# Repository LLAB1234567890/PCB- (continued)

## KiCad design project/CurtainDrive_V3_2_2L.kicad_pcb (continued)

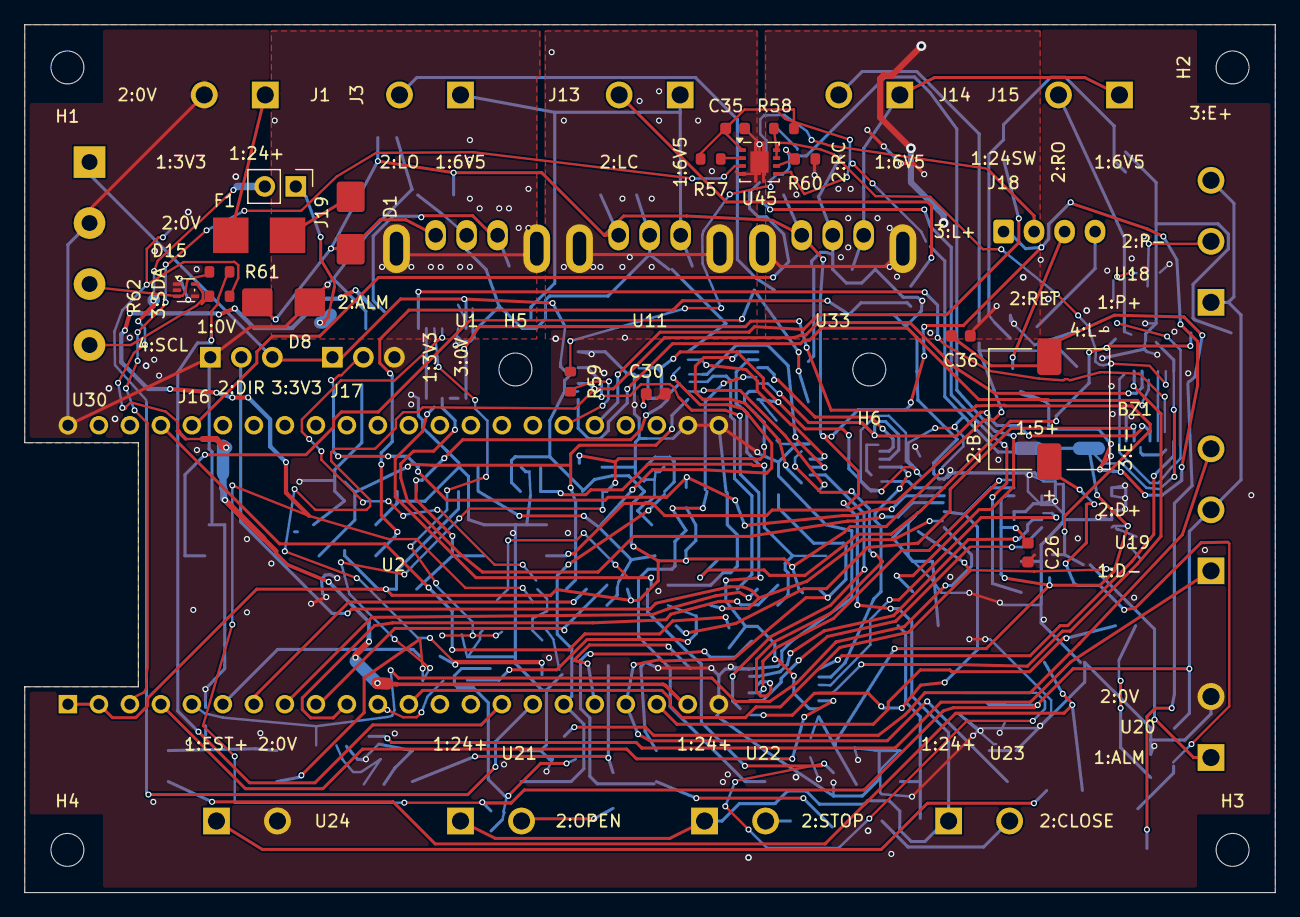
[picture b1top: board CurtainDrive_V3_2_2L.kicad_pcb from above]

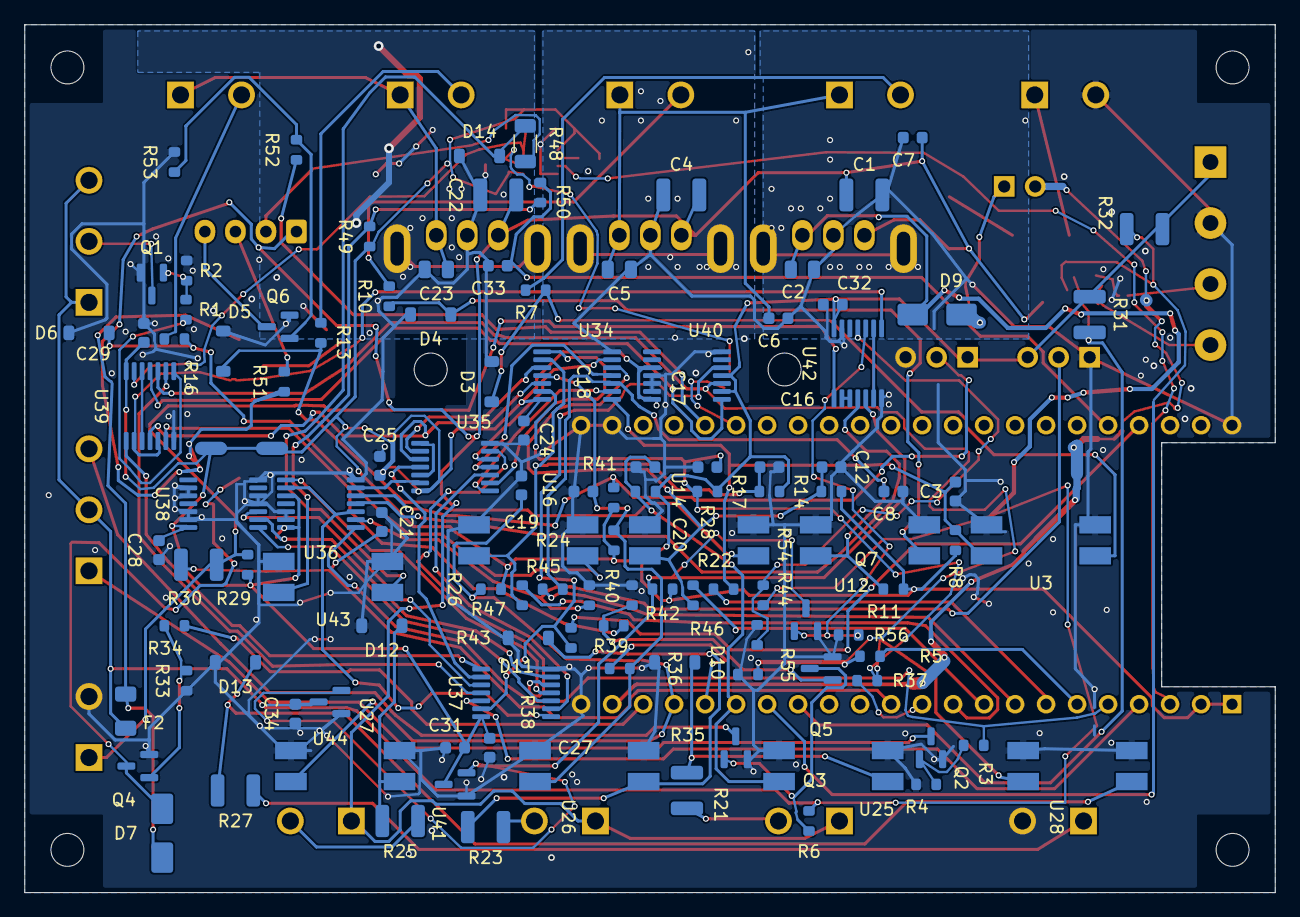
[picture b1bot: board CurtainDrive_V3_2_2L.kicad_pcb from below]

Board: 2 copper layers, 102.5 x 71.1 mm, 157 parts (114 on the bottom side), 110 nets.

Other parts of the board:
H1, H2, H3, H4, H5, H6: M2.5 NPTH; MountingHole_2.7mm_M2.5

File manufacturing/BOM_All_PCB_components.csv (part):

Designator,Value,Footprint,MPN,Manufacturer,LCSC,Assembly,Note
U2,ESP32-S3-DEVKITC-1-N8R8,ESP32_S3_DevKitC_1_N8R8,ESP32-S3-DEVKITC-1-N8R8,ESPRESSIF,C20541519,Manual,"ESP32-S3 DevKitC-1 v1.1 N8R8. GPIO4 STEP, GPIO5 DIR, GPIO6 ARM, GPIO1 RUN feedback, GPIO2 SET, GPIO21 lamp, GPIO47 watchdog. Pads32-34 GPIO35-37 unavailable with PSRAM. J19 power link must be removed for ordinary USB powering."
C1,10uF 100V,C_1210_3225Metric,C3225X7R2A106K250AC,TDK,C3883958,SMT,厂家特性表已核对；10uF标称，需按24V直流偏压复核实际电容
C2,22uF 10V,C_0805_2012Metric,CL21A226MPQNNNE,SAMSUNG(三星),C29277,SMT,
C4,10uF 100V,C_1210_3225Metric,C3225X7R2A106K250AC,TDK,C3883958,SMT,厂家特性表已核对；10uF标称，需按24V直流偏压复核实际电容
C5,22uF 10V,C_0805_2012Metric,CL21A226MPQNNNE,SAMSUNG(三星),C29277,SMT,
C6,100nF 50V,C_0603_1608Metric,CC0603KRX7R9BB104,YAGEO,C14663,SMT,
C7,100nF 50V,C_0603_1608Metric,CC0603KRX7R9BB104,YAGEO,C14663,SMT,
C22,10uF 100V,C_1210_3225Metric,C3225X7R2A106K250AC,TDK,C3883958,SMT,厂家特性表已核对；10uF标称，需按24V直流偏压复核实际电容
C23,22uF 10V,C_0805_2012Metric,CL21A226MPQNNNE,SAMSUNG,C29277,SMT,
D1,SS36-E3/57T,D_SMB,SS36-E3/57T,VISHAY(威世),C35722,SMT,反接保护，阳极2接保险丝，阴极1接板内24V
D8,SMBJ26A,D_SMB,SMBJ26A-13-F,DIODES,C135062,SMT,
D9,SS14,D_SMA,SS14,MDD,C2480,SMT,
F1,1A fast,Source_F1,0451001.MRL,Littelfuse(美国力特),C3099,SMT,
J1,KF301-5.0-2P,Source_J1,KF301-5.0-2P,KEFA(科发),C474881,Manual,
U1,K78U05-1000R3,K78U05_1000R3,K78U05-1000R3,MORNSUN,,Manual,专用独立 CASE 铜岛，手工装配；禁止并联输出
U11,K78UX6-1000R3,K78U05_1000R3,K78UX6-1000R3,MORNSUN,,Manual,专用独立 CASE 铜岛，手工装配；禁止并联输出
U33,K78UX6-1000R3,K78U05_1000R3,K78UX6-1000R3,MORNSUN,,Manual,RC/RO 独立供电；手工装配
C3,10nF 50V,C_0603_1608Metric,0603B103K500NT,FH,C57112,SMT,
C8,10nF 50V,C_0603_1608Metric,0603B103K500NT,FH,C57112,SMT,
C12,10nF 50V,C_0603_1608Metric,0603B103K500NT,FH,C57112,SMT,
C16,10nF 50V,C_0603_1608Metric,0603B103K500NT,FH,C57112,SMT,
D3,1N4148W,D_SOD-123,1N4148W,R+O(宏嘉诚),C7420318,SMT,
D4,1N4148W,D_SOD-123,1N4148W,R+O(宏嘉诚),C7420318,SMT,
D5,1N4148W,D_SOD-123,1N4148W,R+O(宏嘉诚),C7420318,SMT,
D6,1N4148W,D_SOD-123,1N4148W,R+O(宏嘉诚),C7420318,SMT,
J3,KF301-5.0-2P,Source_J3,KF301-5.0-2P,KEFA(科发),C474881,Manual,"SS-01GL2 COM/NC; NO unused. LO. Approx 7mA at 6.5V, no external wetting-load resistor. Open or broken wire = fault."
J13,KF301-5.0-2P,Source_J13,KF301-5.0-2P,KEFA(科发),C474881,Manual,"SS-01GL2 COM/NC; NO unused. LC. Approx 7mA at 6.5V, no external wetting-load resistor. Open or broken wire = fault."
J14,KF301-5.0-2P,Source_J14,KF301-5.0-2P,KEFA(科发),C474881,Manual,"SS-01GL2 COM/NC; NO unused. RC. Approx 7mA at 6.5V, no external wetting-load resistor. Open or broken wire = fault."
J15,KF301-5.0-2P,Source_J15,KF301-5.0-2P,KEFA(科发),C474881,Manual,"SS-01GL2 COM/NC; NO unused. RO. Approx 7mA at 6.5V, no external wetting-load resistor. Open or broken wire = fault."
R7,750R,R_0603_1608Metric,0603WAF7500T5E,UNI-ROYAL,C23241,SMT,
R8,10k,R_0603_1608Metric,0603WAF1002T5E,UNI-ROYAL,C25804,SMT,
R10,750R,R_0603_1608Metric,0603WAF7500T5E,UNI-ROYAL,C23241,SMT,
R11,10k,R_0603_1608Metric,0603WAF1002T5E,UNI-ROYAL,C25804,SMT,
R13,750R,R_0603_1608Metric,0603WAF7500T5E,UNI-ROYAL,C23241,SMT,
R14,10k,R_0603_1608Metric,0603WAF1002T5E,UNI-ROYAL,C25804,SMT,
R16,750R,R_0603_1608Metric,0603WAF7500T5E,UNI-ROYAL,C23241,SMT,
R17,10k,R_0603_1608Metric,0603WAF1002T5E,UNI-ROYAL,C25804,SMT,
U3,EL817S1(C)(TU)-VG,Source_U3,EL817S1(C)(TU)-VG,EVERLIGHT(亿光),C2992765,SMT,
U12,EL817S1(C)(TU)-VG,Source_U12,EL817S1(C)(TU)-VG,EVERLIGHT(亿光),C2992765,SMT,
U14,EL817S1(C)(TU)-VG,Source_U14,EL817S1(C)(TU)-VG,EVERLIGHT(亿光),C2992765,SMT,
U16,EL817S1(C)(TU)-VG,Source_U16,EL817S1(C)(TU)-VG,EVERLIGHT(亿光),C2992765,SMT,
C21,10nF 50V,C_0603_1608Metric,0603B103K500NT,FH,C57112,SMT,
Q1,AO3400A,SOT-23,AO3400A,AOS,C20917,SMT,
Q2,AO3400A,SOT-23,AO3400A,AOS,C20917,SMT,
Q3,AO3400A,SOT-23,AO3400A,AOS,C20917,SMT,
Q5,AO3400A,SOT-23,AO3400A,AOS,C20917,SMT,Enable holding torque when 3V3 power is good and external E-stop is healthy; independent of normal STOP
R1,100R,R_0603_1608Metric,0603WAF1000T5E,UNI-ROYAL,C22775,SMT,
R2,10k,R_0603_1608Metric,0603WAF1002T5E,UNI-ROYAL,C25804,SMT,
R3,100R,R_0603_1608Metric,0603WAF1000T5E,UNI-ROYAL,C22775,SMT,
R4,10k,R_0603_1608Metric,0603WAF1002T5E,UNI-ROYAL,C25804,SMT,
R6,10k,R_0603_1608Metric,0603WAF1002T5E,UNI-ROYAL,C25804,SMT,
R29,10k,R_0603_1608Metric,0603WAF1002T5E,UNI-ROYAL,C25804,SMT,
R30,100k,R_1210_3225Metric,RC1210FR-07100KL,YAGEO,C375531,SMT,100k isolates GPIO8 from hardware alarm raw node; 10nF gives about 1ms input filter
U18,KF301-5.0-3P,Source_U18,KF301-5.0-3P,KEFA(科发),C474882,Manual,
U19,KF301-5.0-3P,Source_U19,KF301-5.0-3P,KEFA(科发),C474882,Manual,
U20,KF301-5.0-2P,Source_J1,KF301-5.0-2P,KEFA(科发),C474881,Manual,1=ALM/P，2=COM-；原三针端子改为两针
C17,10nF 50V,C_0603_1608Metric,0603B103K500NT,FH,C57112,SMT,
C18,10nF 50V,C_0603_1608Metric,0603B103K500NT,FH,C57112,SMT,
C19,10nF 50V,C_0603_1608Metric,0603B103K500NT,FH,C57112,SMT,
C20,10nF 50V,C_0603_1608Metric,0603B103K500NT,FH,C57112,SMT,
D10,1N4148W,D_SOD-123,1N4148W,R+O,C7420318,SMT,
D11,1N4148W,D_SOD-123,1N4148W,R+O,C7420318,SMT,
D12,1N4148W,D_SOD-123,1N4148W,R+O,C7420318,SMT,
D13,1N4148W,D_SOD-123,1N4148W,R+O,C7420318,SMT,
R21,3.3k,R_1210_3225Metric,1210W2J0332T5E,UNI-ROYAL(厚声),C621025,SMT,
R22,10k,R_0603_1608Metric,0603WAF1002T5E,UNI-ROYAL,C25804,SMT,
R23,3.3k,R_1210_3225Metric,1210W2J0332T5E,UNI-ROYAL(厚声),C621025,SMT,
R24,10k,R_0603_1608Metric,0603WAF1002T5E,UNI-ROYAL,C25804,SMT,
R25,3.3k,R_1210_3225Metric,1210W2J0332T5E,UNI-ROYAL(厚声),C621025,SMT,
R26,10k,R_0603_1608Metric,0603WAF1002T5E,UNI-ROYAL,C25804,SMT,
R27,3.3k,R_1210_3225Metric,1210W2J0332T5E,UNI-ROYAL(厚声),C621025,SMT,
R28,10k,R_0603_1608Metric,0603WAF1002T5E,UNI-ROYAL,C25804,SMT,
R36,100k,R_0603_1608Metric,0603WAF1003T5E,UNI-ROYAL,C25803,SMT,隔开MCU与硬件停机节点；GPIO12/18须纯输入、禁用内部上下拉
R37,100k,R_0603_1608Metric,0603WAF1003T5E,UNI-ROYAL,C25803,SMT,隔开MCU与硬件停机节点；GPIO12/18须纯输入、禁用内部上下拉
U21,KF301-5.0-2P,Source_U21,KF301-5.0-2P,KEFA(科发),C474881,Manual,绿色 LAY711BN32 的 NO 触点，开帘
U22,KF301-5.0-2P,Source_U22,KF301-5.0-2P,KEFA(科发),C474881,Manual,红色 LAY711BN42 的 NC 触点；按下或断线均停止
U23,KF301-5.0-2P,Source_U23,KF301-5.0-2P,KEFA(科发),C474881,Manual,黑色 LAY711BN22 的 NO 触点，关帘
U24,KF301-5.0-2P,Source_U24,KF301-5.0-2P,KEFA(科发),C474881,Manual,接板外两路急停NC串联之后、K1线圈A1的24V节点；不再接驱动器母线；仅检测，不承载电机功率
U25,EL817S1(C)(TU)-VG,Source_U25,EL817S1(C)(TU)-VG,EVERLIGHT(亿光),C2992765,SMT,
U26,EL817S1(C)(TU)-VG,Source_U26,EL817S1(C)(TU)-VG,EVERLIGHT(亿光),C2992765,SMT,
U27,EL817S1(C)(TU)-VG,Source_U27,EL817S1(C)(TU)-VG,EVERLIGHT(亿光),C2992765,SMT,
U28,EL817S1(C)(TU)-VG,Source_U28,EL817S1(C)(TU)-VG,EVERLIGHT(亿光),C2992765,SMT,
BZ1,KLJ-9650-5Y,KLJ_9650_5Y,KLJ-9650-5Y,KELIKING,C18186314,SMT,Internal actualSMT active buzzer; positive pad1. Reflow curve/cleaning per manufacturer.
D7,SS14,D_SMA,SS14,MDD,C2480,SMT,
F2,PTC 0.35A,Fuse_1206_3216Metric,1206L035/16YR,Littelfuse,C126817,SMT,
Q4,AO3400A,SOT-23,AO3400A,AOS,C20917,SMT,
R31,4.7k,R_1210_3225Metric,1210W2J0472T5E,UNI-ROYAL(厚声),C26060,SMT,
R32,4.7k,R_1210_3225Metric,1210W2J0472T5E,UNI-ROYAL(厚声),C26060,SMT,
R33,10k,R_0603_1608Metric,0603WAF1002T5E,UNI-ROYAL,C25804,SMT,
R34,100R,R_0603_1608Metric,0603WAF1000T5E,UNI-ROYAL,C22775,SMT,
U30,KF301-5.0-4P,KF301_5_0_4P,KF301-5.0-4P,KEFA(科发),C5350152,Manual,"1=3V3, 2=GND, 3=SDA, 4=SCL"
U34,SN74LVC14APWR,TSSOP-14_4.4x5mm_P0.65mm,SN74LVC14APWR,TI,C7663,SMT,
U35,SN74LVC08APWR,TSSOP-14_4.4x5mm_P0.65mm,SN74LVC08APWR,TI,C465737,SMT,
U36,SN74LVC86APWR,TSSOP-14_4.4x5mm_P0.65mm,SN74LVC86APWR,TI,C350562,SMT,
U37,SN74LVC08APWR,TSSOP-14_4.4x5mm_P0.65mm,SN74LVC08APWR,TI,C465737,SMT,
U38,SN74LVC32APWR,TSSOP-14_4.4x5mm_P0.65mm,SN74LVC32APWR,TI,C352974,SMT,
U39,SN74LVC08APWR,TSSOP-14_4.4x5mm_P0.65mm,SN74LVC08APWR,TI,C465737,SMT,
U40,SN74LVC74APWR,TSSOP-14_4.4x5mm_P0.65mm,SN74LVC74APWR,TI,C350561,SMT,"Asynchronous clear, D=1; only a fresh GPIO6 rising edge after healthy inputs may re-arm. Unused flip-flop is held cleared."
U41,TLV803EA30DBZR,SOT-23,TLV803EA30DBZR,TI,C5218924,SMT,"Pin1 GND,2 RESET open-drain,3 VDD.3V3 falling threshold raised above ESP32 minimum3.0V."
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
